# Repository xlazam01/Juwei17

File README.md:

<div align="center">
  <h1>Juwei17 Mount Upgrade</h1>
  
</div>

## 🚀 Project Overview

This repository contains subprojects to upgrade the Juwei17 mount with enhanced hardware, software, and mechanics. The goal is to provide a modern, feature-rich, and user-friendly experience for astronomy enthusiasts.

---

## 🧑‍🔧 Skills Needed

 - Project is very DIY oriented
 - PCB is very dense and it is recommended to manufacture it via some service (JLCPCB or similar)
 - Some soldering (hall sensors, BME280, switch, connector crimping)

---

## ✨ Upgrade Features

- **Larger on/off switch**
- **Homing**
- **GPS**
- **Weather sensors**
- **Fast slewing possible**
- **Support for TMC SPI or UART modules**  
  (TMC2209, TMC2130, TMC5160, etc.)
- **USB-C connector**
- **Programming button** (no ST-Link needed)
- **Loader application** (semi-automatic programming for OnStep and SWS)

---

## 🧩 Hardware Features

- Minimized PCB size
- Support for Home and Limit switches
- OnWire interface
- GPS interface
- STM32F446 as main processor
- Power switch not needed:
  - Mount will start without switch connected
  - No high current goes through switch itself
  - When switch is closed, mount is off

---

## 💾 Software Features

- Based on OnStepX (preconfigured, just upload)
- Added STM32 RTC support
- Modified Weather:
  - Due to excessive BME self-heating
  - Temperature from DS1820
  - Humidity and pressure from BME280
- TLS fallback (STM32 → GPS)
- PlatformIO is used for OnStepX - My preferred IDE
- Arduino for SWS - due to specific version of ESP toolchain needed

---

## 🏗️ Mechanics

- CAD files
- STL files for 3D printing new covers

---

## 📦 Required Components

- New hardware - data on this github repo
- 2x TMC Drivers - you can reuse TMC2209 from your original main board
  - TMC2209 UART - [link](https://www.aliexpress.com/item/33028050145.html)
  - TMC2130 SPI - [link](https://www.aliexpress.com/item/32970150483.html)
  - TMC5160 SPI - [link](https://www.aliexpress.com/item/1005006043696147.html)
- Beitian BK-280 GPS module -  [link](https://www.aliexpress.com/item/1005009032383874.html)
- BME280 module - [link](https://www.aliexpress.com/item/1005007070789246.html)
- DS1820 - [link](https://www.aliexpress.com/item/1005009032259334.html)
- 2× 3144 hall sensors for homing functionality [link](https://www.aliexpress.com/item/1005008305500149.html)
- 16mm antivandal switch - 16mm, 12-24V, latching - [link](https://www.aliexpress.com/item/1005007144363231.html)
- Wires, connectors, hot glue, etc.
- Crimping pliers (Iwiss IWS-2820M)
- Magnetic rings:
  - Magnets 20×5×2mm [link](https://www.aliexpress.com/item/1005009668801201.html)
    ⚠️ *Warning: Large deviation in sizes experienced!*
- Screws M2×6 Voron style self-tapping screws - [link](https://www.aliexpress.com/item/1005003604942716.html)
- 4x M3x16, 4x  M3x10 countersunk
- optional 3144 hall sensor module for test [link](https://www.aliexpress.com/item/1005009110720818.html)
  - 5V power
  - It can help you to check polarity and sensitivity for you DIY magnet rings

---

## 🛠️ Building Tips

- Use hot glue to fix hall sensors and wires
- Mind the hall sensor "polarity" and magnets orientation in rings - good to check with dry run before mounting everything together

---

## 📁 Folder Description

- **CAD**: SolidEdge models (`*.par` files)
- **HW**: KiCad files (design and schematic PDF)
- **Images**: Build images
- **OnstepEspLoader**: Python app to support you through flashing process
- **OnStepX**: OnStep code (PlatformIO and VSCode)
- **SmartWebServer**: ESP8266 code (built in Arduino due to specific Espressif version)
- **STLs**: Files for 3D printing

---

## 📝 ToDo

- PEC

---

## 🖼️ Photo Gallery
<div align="center">
    
</div>

<div align="center">

</div>
<div align="center">

</div>
<div align="center">

</div>
<div align="center">

</div>
<div align="center">

</div>
<div align="center">

</div>

---

## 🛠️ Assembly Instructions

1. **Print the required parts.**
2. **Prepare magnets for the magnet rings:**
    - Ensure all magnets are oriented in the same direction.
    - Take care to prevent magnets from snapping together unexpectedly.
    - Test magnet polarity using a 3144 module or a bare sensor.
3. **Insert magnets into the rings.**
    - Fill roughly 90-180degrees
4. **Secure magnets with a thin layer of epoxy.**
    - 5min epoxy is ideal
5. **Assemble the front cover using small screws.**
    - Put together PCB_holder and front_panel
6. **Install hall sensors and wiring into the new cover.**
    - Insert hall sensor with right orientation (double check)
    - Fix them in place with hotglue
7. **Mount the new 16mm switch and do wiring.**
    - We use NO contact for mount ON, NC contact for mount OFF
    - Switch backlight is connected to mainboard
8. **Prepare and install wiring for the GPS and BME280 modules.**
    - Solder longer wires and cut them later to perfect length for BME280
    - For GPS just cut the wire to perfect length
    - Install modules in cavities
    - Fix GPS with GPS_holder and small screws
9. **Install the DS1820 sensor in the second cover.**
    - Pressfit the sensor in place
    - Cut wires to size
10. **Secure all wires with hot glue.**
    - Aim is to not have wires getting pinched during cover installation
11. **Trim wires to length and crimp connectors.**
12. **Plug in jumper for UART/SPI TMC**
13. **Insert TMC modules**
14. **PCB installation**
    - Reuse brass standoff - insert them into holes in front cover
    - Attach the PCB to these standoffs    
15. **Connect all components together.**
    - Install back cover
    - Plug in all connectors
    - Install front cover
    - Screw in four screws for the PCB from the bottom of the mount
16. **Assembly complete!**

---

<div align="center">
    
</div>

## 💻 Firmware Upload

1. **Power off the device.**
2. **Press and hold the button** next to the power connector.
3. **Power on the device.**
4. **Observe the LEDs:**
    - OnStep status LED will be off.
    - WiFi LED will blink if firmware is present; if the ESP is empty, both LEDs will be off.
5. **Start the OnstepEspLoader Python app.**
6. **Select the correct TMC module type.**
7. **Choose homing**
8. **Click "Check STM32":**
    - The bootloader should respond.
    - If it fails, click again.
9. **Click "Upload STM32":**
    - Firmware upload will start.
10. **Wait for the OnStep status LED:**
    - It should turn on after some time.
    - The first boot may take longer as EEPROM is being formatted.
11. **Click "Check OnStep":**
    - It should respond with name and version.
12. **Switch to SWS mode:**
    - OnStep enters transparent mode and is ready to upload ESP firmware.
13. **Click "Upload ESP":**
    - Firmware for the webserver will be uploaded to the ESP.
14. **Finish:**
    - A soft reset will occur after some time, or you can power cycle the device manually.

---

## ⚙️ Default Firmware Configuration

Default firmware configuration expects:
- BME280, DS1820 - if initialization fails, there will be no weather information on webserver
- TMC2209, TMC5160 or TMC2130 - according to selected firmware during programming
- Correct polarity of HAL sensors for homing - if not fulfilled, homing will not work correctly
- Motor current is set to 1.0A for RUN and 1.3A for GOTO
- Homing sense is HIGH

---

## 🏗️ Build Your Own OnStepX

- If you use OnStepX from Howard Dutton - there will be no support for STM32 RTC (time and date will not be stored) and weather service will provide false temperatures from BME280 (self-heating)
 - This could be potentially merged into main branch (I know that STM32 RTC was not planned - there are no official boards ready for this, weather fix is open)
- For my Juwei17 board use the OnStepX from this repository
- Change configuration as needed
- For upload use Serial Bootloader - depending on your IDE (Arduino, PlatformIO) how to do it 
- There are three pads on the bottom of the PCB to connect to ST-Link - you need to solder wires or a connector with 2mm pitch
- If you want to use OnstepEspLoader just browse for your STM32 firmware binary
- Binary file pattern:

| Firmware Name         | TMC Module | Homing      |
|-----------------------|------------|-------------|
| firmware_5160_wH      | TMC5160    | With Homing |
| firmware_5160_woH     | TMC5160    | Without Homing |
| firmware_2130_wH      | TMC2130    | With Homing |
| firmware_2130_woH     | TMC2130    | Without Homing |
| firmware_2209_wH      | TMC2209    | With Homing |
| firmware_2209_woH     | TMC2209    | Without Homing |

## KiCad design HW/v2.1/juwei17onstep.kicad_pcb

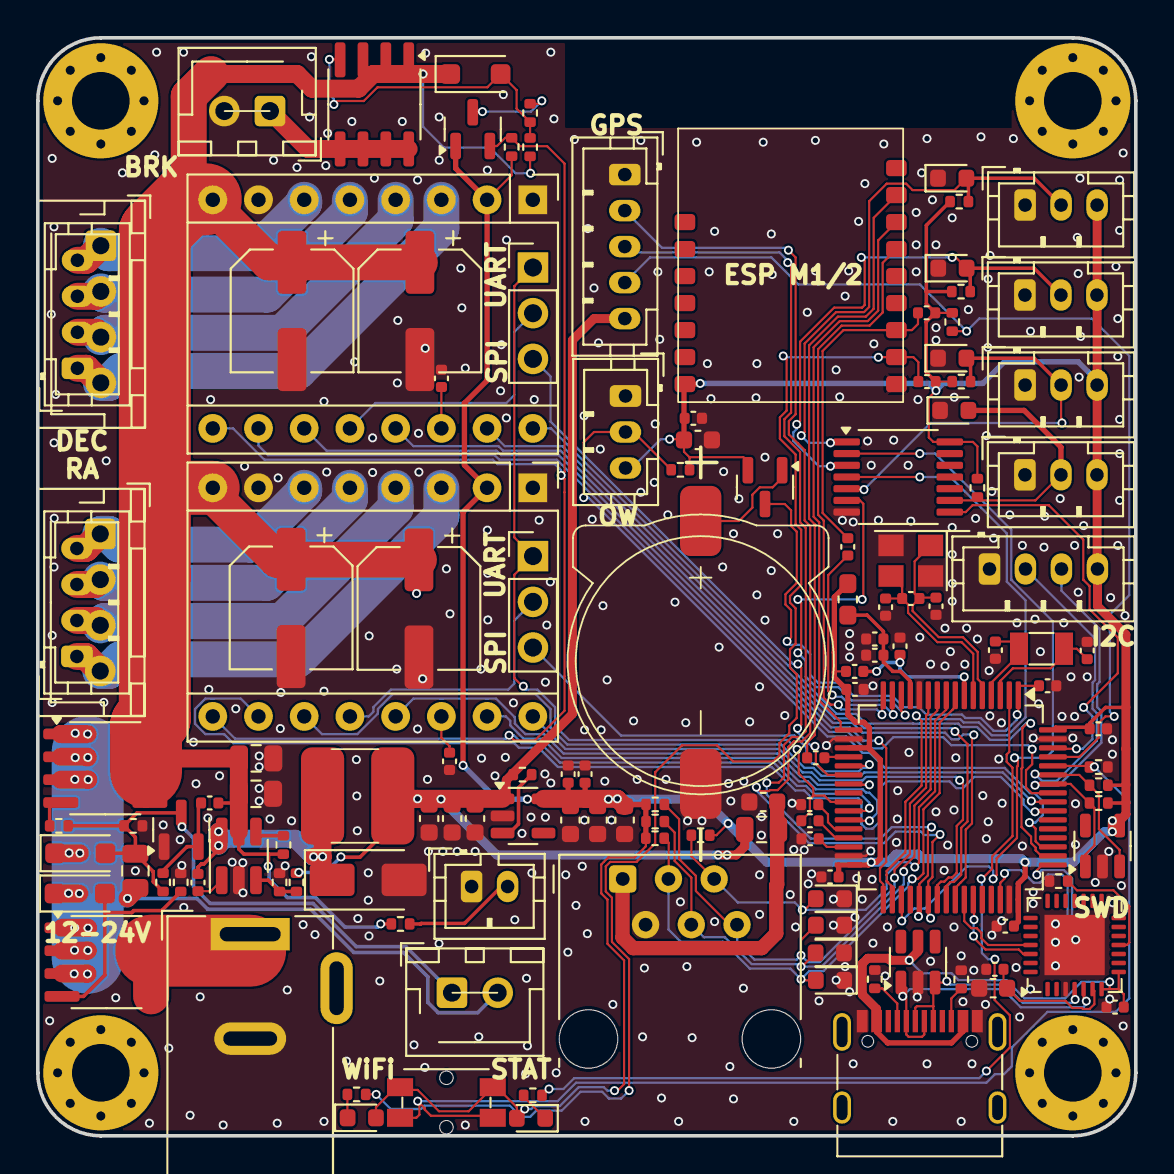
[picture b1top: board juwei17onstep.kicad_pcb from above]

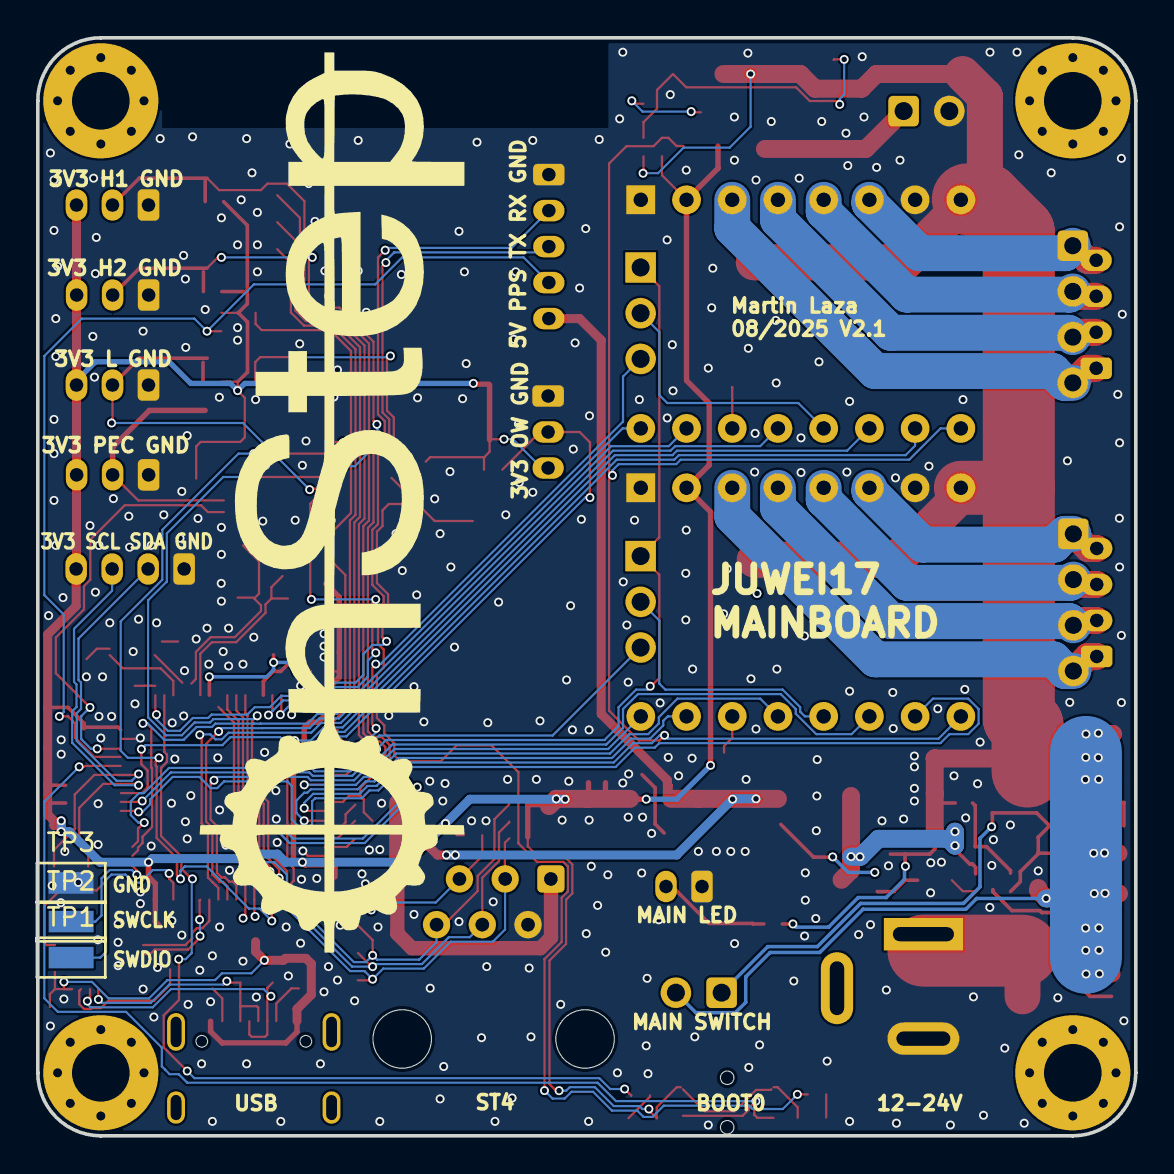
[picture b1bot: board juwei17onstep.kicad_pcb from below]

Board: 2 copper layers, 61.0 x 61.0 mm, 139 parts (3 on the bottom side), 97 nets.

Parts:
A1, A2: Pololu_Breakout_A4988; StepStick
BT1: Battery_Cell; CR1220_holder
C1, C4: 20pF; C_0402_1005Metric
C2, C19: 10u/25V; C_0805_2012Metric
C3, C11, C14, C15, C16, C18, C22, C26, C49: 10uF/10V; C_0603_1608Metric
C5, C13: 1uF/10V; C_0402_1005Metric
C6, C7: 2u2/6.3; C_0402_1005Metric
C8, C9: 12pF; C_0402_1005Metric
C10, C12, C20, C21, C40, C46, C47: 100n; C_0402_1005Metric
C17, C23, C41: 100n/50V; C_0402_1005Metric
C24: 1u/25V; C_0805_2012Metric
C25: 1uF; C_0402_1005Metric
C27: 100nF; C_0402_1005Metric
C28, C42, C43, C44: 100uF/35V; CP_Elec_6.3x7.7
D1, D15: LED; LED_0603_1608Metric
D2: SS34; D_SMA
D3, D4, D5, D6, D8, D9, D10, D14: 0603ESDA-05N; D_0603_1608Metric
D7, D16: BZT52B12; D_SOD-123F
D11: BZT52Bxx; D_SOD-123F
D13: BAT54C; SOT-23
D17: BAV99; SOT-23
F1: SMD0805P050TF; Fuse_0805_2012Metric
H1, H2, H3, H4: MountingHole; MountingHole_3.2mm_M3_Pad_Via
J1: USB_C_Receptacle_USB2.0; USB_C_Receptacle_G-Switch_GT-USB-7010ASV
J2: RJ12; RJ12_Amphenol_54601-x06_Horizontal
J3: 5.5/2.1 Barell DC3; BarrelJack_Wuerth_6941xx301002
J4: RA_HOME; JST_PH_B3B-PH-K_1x03_P2.00mm_Vertical
J5: DEC_HOME; JST_PH_B3B-PH-K_1x03_P2.00mm_Vertical
J6: LIMIT; JST_PH_B3B-PH-K_1x03_P2.00mm_Vertical
J7: GPS; JST_PH_B5B-PH-K_1x05_P2.00mm_Vertical
J8: Conn_01x02; JST_1x02_P2.54
J10: MAIN SWITCH; JST_1x02_P2.54
J11, J12: RA_2mm; JST_PH_B4B-PH-K_1x04_P2.00mm_Vertical
J13, J14: RA_2.54mm; JST_1x04_P2.54
J15: I2C; JST_PH_B4B-PH-K_1x04_P2.00mm_Vertical
J16: LED CONNECTOR; JST_PH_B2B-PH-K_1x02_P2.00mm_Vertical
J17: PEC; JST_PH_B3B-PH-K_1x03_P2.00mm_Vertical
J18: ONEWIRE; JST_PH_B3B-PH-K_1x03_P2.00mm_Vertical
JP1, JP2: SolderJumper_3_Open; PinHeader_1x03_P2.54mm_Vertical
L2: FNR5040S100MT; L_5.5x5.1mm
L3: BLM18HE601SH1D; L_0603_1608Metric_Pad1.05x0.95mm_HandSolder
Q1, Q2, Q4: AO4411; SOIC-8_3.9x4.9mm_P1.27mm
Q3: DTC114E; SOT-23
R1: 1MEG; C_0402_1005Metric
R2, R3, R4, R5, R36, R37: 10k; C_0402_1005Metric
R6, R21, R25, R26, R27, R33, R34, R38: 10k; R_0402_1005Metric
R7, R8, R39: 5k1; R_0402_1005Metric
R9, R18, R44, R45: 1k; R_0402_1005Metric
R10, R11, R31, R43: 100k; R_0402_1005Metric
R14: 36k; R_0402_1005Metric
R15: 6k8; R_0402_1005Metric
R16, R17, R19, R32: 4k7; R_0402_1005Metric
R20, R22, R23, R24: 2k4; R_0402_1005Metric
R28, R29, R42: 1k; C_0402_1005Metric
R35: 510R; R_0402_1005Metric
RST2: EVQPUM; Panasonic_EVQPUM_EVQPUD
TP1, TP2, TP3: TestPoint; TestPoint_Keystone_5015_Micro-Minature
U1: ESP_M2
U2: CP2102N-Axx-xQFN28; QFN-28-1EP_5x5mm_P0.5mm_EP3.35x3.35mm
U5: USBLC6-2SC6; SOT-23-6
U6: 74HC14; TSSOP-14_4.4x5mm_P0.65mm
U7: ME6211; SOT-23-5
U8: ME3116; SOT-23-6_Handsoldering
U9: 24AA64T-I/OT; SOT-23-5
U12: STM32F446RETx; LQFP-64_10x10mm_P0.5mm
Y1: TAXM8M4RDBCCT2T / 8MHz 3225; Crystal_SMD_3225-4Pin_3.2x2.5mm
Y2: Crystal; Crystal_SMD_3215-2Pin_3.2x1.5mm

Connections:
/3V3: A1.2 (VDD), A2.2 (VDD), C10.1, C12.1, C13.2, C14.2, C15.2, C16.2, C20.1, C21.1, C22.2, C40.1, C41.2, D1.2 (A), D13.2, D15.2 (A), J4.3, J5.3, J6.3, J15.4, J17.3, J18.3, L3.1, Q3.1 (B), R2.2, R3.2, R5.2, R16.2, R17.2, R19.2, R20.2, R22.2, R23.2, R24.2, R25.2, R26.2, R27.2, R33.2, R34.2, R38.2, RST2.2, U1.7 (VCC), U6.14 (VCC), U7.5 (OUT), U9.4 (V_{CC}), U12.19 (VDD), U12.32 (VDD), U12.48 (VDD), U12.64 (VDD)
/DEC/DIR: A2.16 (DIR), U12.50 (PA15)
/DEC/ENN: A1.9 (~ENABLE), A2.9 (~ENABLE), Q3.2 (E), R38.1, U12.26 (PB0)
/DEC/M0: A2.10 (CFG1), U12.57 (PB5)
/DEC/M1: A2.11 (CFG2), U12.33 (PB12)
/DEC/M2: JP2.3 (B), U12.22 (PA6)
/DEC/M3: A2.13 (CFG0), U12.41 (PA8)
/DEC/STEP: A2.15 (STEP), U12.40 (PC9)
/DEC/TMC_UART: JP1.1 (A), JP2.1 (A), R42.1, U12.25 (PC5)
/DEC/VM: A1.8 (VMOT), A2.8 (VMOT), C2.1, C19.1, C23.2, C28.1, C42.1, C43.1, C44.1, D11.1 (K), Q2.1 (S), Q2.2 (S), Q2.3 (S), Q4.5 (D), Q4.6 (D), Q4.7 (D), Q4.8 (D), R10.2, R31.2, R35.2, U8.5 (VIN)
/ESP_BOOT: R29.2, U12.15 (PA1)
/ESP_RST: R28.1, U12.20 (PA4)
/ESP_RXD: U1.13 (RXD0), U12.16 (PA2)
/ESP_TXD: U1.14 (TXD0), U12.17 (PA3)
/GPS_RXD: J7.2, U12.38 (PC7)
/GPS_TXD: J7.3, U12.37 (PC6)
/ME3116/VOUT: C3.2, C18.2, C49.2, F1.2, J7.5, L2.2, R11.2, R14.2, U7.1 (IN)
/OnStep_MaxSTM/AXIS1_DIR: A1.16 (DIR), U12.39 (PC8)
/OnStep_MaxSTM/AXIS1_HOME_SW: U6.2, U12.35 (PB14)
/OnStep_MaxSTM/AXIS1_M0: A1.10 (CFG1), U12.55 (PB3)
/OnStep_MaxSTM/AXIS1_M1: A1.11 (CFG2), U12.56 (PB4)
/OnStep_MaxSTM/AXIS1_M2: JP1.3 (B), U12.21 (PA5)
/OnStep_MaxSTM/AXIS1_M3: A1.13 (CFG0), U12.23 (PA7)
/OnStep_MaxSTM/AXIS1_STEP: A1.15 (STEP), U12.27 (PB1)
/OnStep_MaxSTM/AXIS2_HOME_SW: U6.4, U12.34 (PB13)
/OnStep_MaxSTM/BOOT0: R6.2, RST2.1, U12.60 (BOOT0)
/OnStep_MaxSTM/LIMIT_SW: U6.6, U12.14 (PA0)
/OnStep_MaxSTM/M: J1.A7 (D-), J1.B7 (D-), U2.5 (D-), U5.1 (I/O1)
/OnStep_MaxSTM/NRST: C5.1, R2.1, U12.7 (NRST)
/OnStep_MaxSTM/ONEWIRE: J18.2, R19.1, U12.51 (PC10)
/OnStep_MaxSTM/OSC32_IN: C8.1, U12.3 (PC14), Y2.1
/OnStep_MaxSTM/OSC32_OUT: C9.1, U12.4 (PC15), Y2.2
/OnStep_MaxSTM/OSCIN: C1.1, R1.1, U12.5 (PH0), Y1.1
/OnStep_MaxSTM/OSCOUT: C4.1, R1.2, U12.6 (PH1), Y1.3
/OnStep_MaxSTM/P: J1.A6 (D+), J1.B6 (D+), U2.4 (D+), U5.3 (I/O2)
/OnStep_MaxSTM/PEC_SENSE: U6.8, U12.62 (PB9)
/OnStep_MaxSTM/RX1: U2.26 (TXD), U12.43 (PA10)
/OnStep_MaxSTM/SCL: J15.3, R17.1, U9.1 (SCL), U12.58 (PB6)
/OnStep_MaxSTM/SDA: J15.2, R16.1, U9.3 (SDA), U12.59 (PB7)
/OnStep_MaxSTM/ST4_DEC_N: D5.2 (A2), J2.5, R23.1, U12.9 (PC1)
/OnStep_MaxSTM/ST4_DEC_S: D4.2 (A2), J2.4, R22.1, U12.10 (PC2)
/OnStep_MaxSTM/ST4_RA_E: D6.2 (A2), J2.6, R24.1, U12.11 (PC3)
/OnStep_MaxSTM/ST4_RA_W: D3.2 (A2), J2.3, R20.1, U12.8 (PC0)
/OnStep_MaxSTM/STATUS_LED: R9.1, U12.2 (PC13)
/OnStep_MaxSTM/SWCLK: TP2.1, U12.49 (PA14)
/OnStep_MaxSTM/SWDIO: TP1.1, U12.46 (PA13)
/OnStep_MaxSTM/TX1: U2.25 (RXD), U12.42 (PA9)
/OnStep_MaxSTM/VBATT: C47.1, D13.3, U12.1 (VBAT)
/OnStep_MaxSTM/VBUS: C25.2, J1.A4 (VBUS), J1.A9 (VBUS), J1.B4 (VBUS), J1.B9 (VBUS), U2.7 (VREGIN), U2.8 (VBUS), U5.5 (VBUS)
/OnStep_MaxSTM/VREF: C7.1, C46.1, L3.2, U12.13 (VDDA)
/PPS: J7.4, R34.1, U12.61 (PB8)
/VBAT: BT1.1 (+), D13.1
GND: A1.1 (GND), A1.7 (GND), A2.1 (GND), A2.7 (GND), BT1.2 (-), C1.2, C2.2, C3.1, C4.2, C5.2, C6.2, C7.2, C8.2, C9.2, C10.2, C11.2, C12.2, C13.1, C14.1, C15.1, C16.1, C18.1, C19.2, C20.2, C21.2, C22.1, C25.1, C26.2, C27.2, C28.2, C40.2, C41.1, C42.2, C43.2, C44.2, C46.2, C47.2, C49.1, D2.2 (A), D3.1 (A1), D4.1 (A1), D5.1 (A1), D6.1 (A1), D8.1 (A1), D9.1 (A1), D10.1 (A1), D14.1 (A1), D17.1 (K), J1.A1 (GND), J1.A12 (GND), J1.B1 (GND), J1.B12 (GND), J2.2, J3.2, J4.1, J5.1, J6.1, J7.1, J8.2, J15.1, J16.1, J17.1, J18.1, R4.1, R6.1, R7.2, R8.2, R15.1, R21.1, R36.1, R37.1, R39.1, R43.2, TP3.1, U1.8 (GND), U2.3 (GND), U2.29 (GND), U5.2 (GND), U6.7 (GND), U7.2 (GND), U8.2 (GND), U9.2 (V_{SS}), U12.12 (VSSA), U12.18 (VSS), U12.31 (VSS), U12.47 (VSS), U12.63 (VSS), Y1.2, Y1.4
unnamed: A1.4 (1A), J11.2, J13.3
unnamed: A1.3 (1B), J11.1, J13.4
unnamed: A1.5 (2A), J11.3, J13.2
unnamed: A1.6 (2B), J11.4, J13.1
unnamed: A1.12 (CFG3), JP1.2 (C)
unnamed: A1.14 (CLK), R36.2
unnamed: A2.4 (1A), J12.2, J14.3
unnamed: A2.3 (1B), J12.1, J14.4
unnamed: A2.5 (2A), J12.3, J14.2
unnamed: A2.6 (2B), J12.4, J14.1
unnamed: A2.12 (CFG3), JP2.2 (C)
unnamed: A2.14 (CLK), R37.2
unnamed: C11.1, F1.1, J2.1
unnamed: D1.1 (K), R9.2
unnamed: C17.2, D2.1 (K), L2.1, U8.6 (SW)
unnamed: D7.2 (A), Q1.4 (G), R21.2
unnamed: D8.2 (A2), J4.2, R25.1, U6.1
unnamed: D9.2 (A2), J5.2, R26.1, U6.3
unnamed: D10.2 (A2), J6.2, R27.1, U6.5
unnamed: D11.2 (A), Q2.4 (G), R31.1, R32.2
unnamed: D14.2 (A2), J17.2, R33.1, U6.9
unnamed: D15.1 (K), R18.2
unnamed: C24.2, D16.2 (A), D17.3 (K), J10.1, R43.1, R44.1, R45.2
unnamed: C24.1, D7.1 (K), D16.1 (K), J10.2, Q1.1 (S), Q1.2 (S), Q1.3 (S), Q4.1 (S), Q4.2 (S), Q4.3 (S)
unnamed: C23.1, D17.2 (A), R45.1
unnamed: J1.A5 (CC1), R7.1
unnamed: J1.B5 (CC2), R8.1
unnamed: J3.1, Q1.5 (D), Q1.6 (D), Q1.7 (D), Q1.8 (D)
unnamed: J8.1, Q2.5 (D), Q2.6 (D), Q2.7 (D), Q2.8 (D)
unnamed: J16.2, R35.1
unnamed: Q3.3 (C), R32.1
unnamed: Q4.4 (G), R44.2
unnamed: R3.1, R29.1, U1.10 (IO0)
unnamed: R5.1, R18.1, U1.9 (IO2)
unnamed: R28.2, U1.15 (RST)
unnamed: C26.1, C27.1, U2.6 (VDD)
unnamed: R39.2, U2.11 (~SUSPEND)
unnamed: R11.1, U7.3 (EN)
unnamed: C17.1, U8.1 (BS)
unnamed: R10.1, U8.4 (EN)
unnamed: R14.1, R15.2, U8.3 (FB)
unnamed: R4.2, U12.28 (PB2)
unnamed: R42.2, U12.29 (PB10)
unnamed: C6.1, U12.30 (VCAP_1)

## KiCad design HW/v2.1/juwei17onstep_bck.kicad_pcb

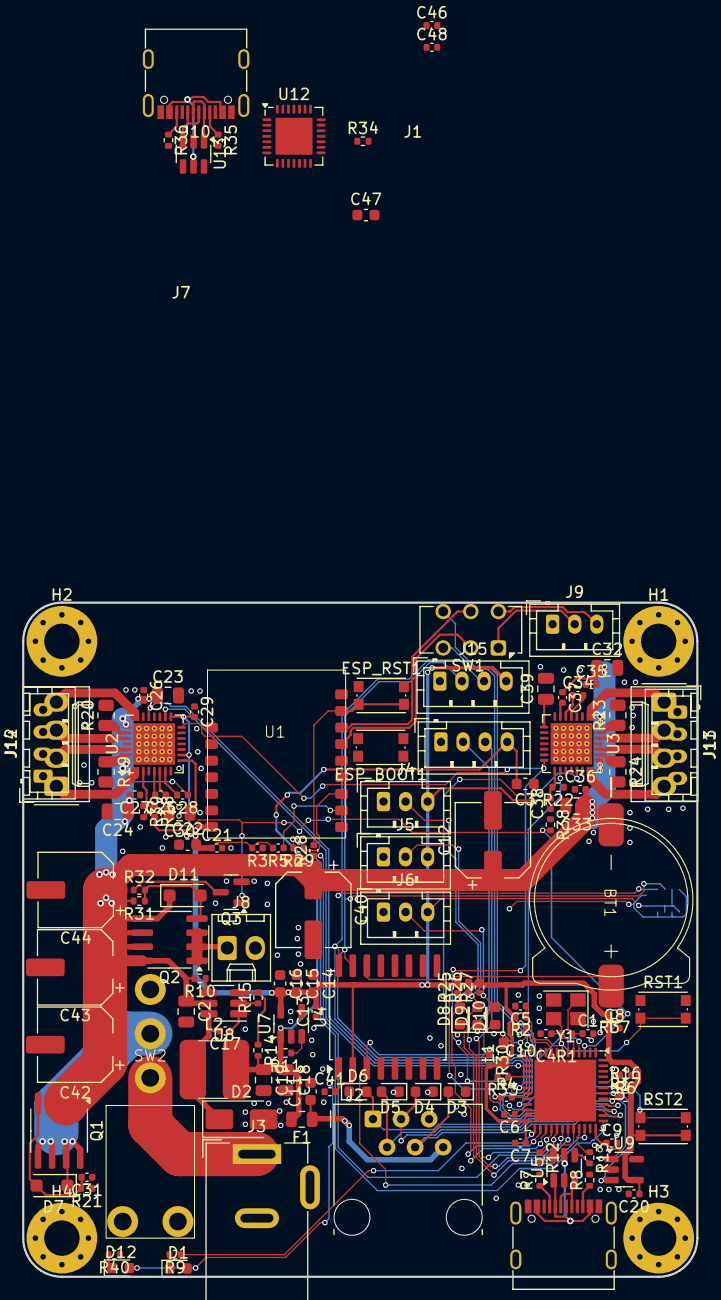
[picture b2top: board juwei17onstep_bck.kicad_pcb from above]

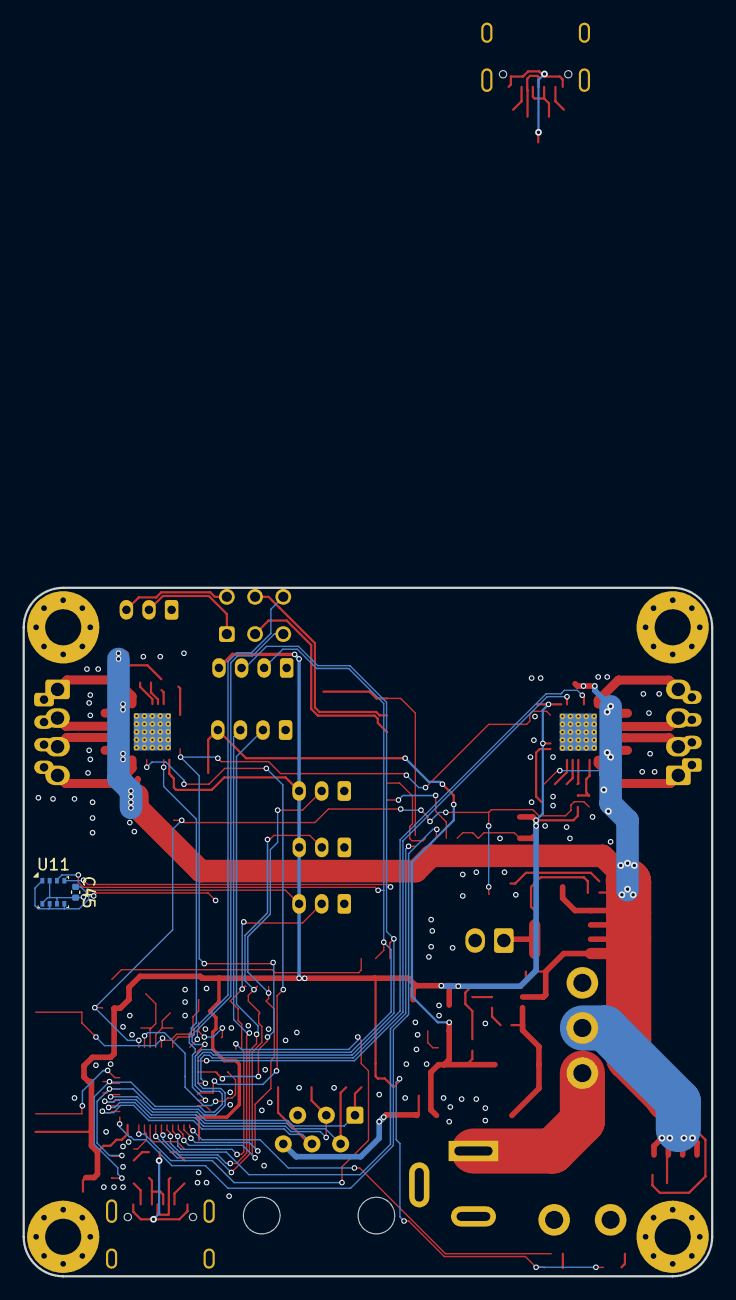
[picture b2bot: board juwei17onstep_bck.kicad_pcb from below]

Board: 2 copper layers, 61.0 x 61.0 mm, 145 parts (2 on the bottom side), 96 nets.

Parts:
BT1: Battery_Cell; CR1220_holder
C1, C4: 20pF; C_0402_1005Metric
C2, C18, C19: 10u/25V; C_0805_2012Metric
C3, C11, C14, C15, C16, C22, C47: 10uF/10V; C_0603_1608Metric
C5, C13: 1uF/10V; C_0402_1005Metric
C6: 2u2/6.3; C_0402_1005Metric
C7, C8, C9, C10, C20, C21: 100n; C_0402_1005Metric
C12, C40, C42, C43, C44: 100uF/35V; CP_Elec_6.3x7.7
C17: 100n/50V/0603; C_0402_1005Metric
C23, C24, C30, C32, C33, C39: 4.7u/25V; C_0805_2012Metric
C25, C31, C34: 22n/50V; C_0402_1005Metric
C26, C27, C28, C29, C35, C36, C37, C38, C41: 100n/50V; C_0402_1005Metric
C45, C48: 100nF; C_0402_1005Metric
C46: 1uF; C_0402_1005Metric
D1, D12: LED; LED_0603_1608Metric
D2: SS34; D_SMA
D3, D4, D5, D6, D8, D9, D10: 0603ESDA-05N; D_0603_1608Metric
D7: BZT52B12; D_SOD-123F
D11: BZT52Bxx; D_SOD-123F
ESP_BOOT1: EVQPUM; SW_Push_1P1T_NO_CK_KMR2
ESP_RST1: EVQPUM; SW_Push_1P1T_NO_CK_KMR2
F1: SMD0805P050TF; Fuse_0805_2012Metric
H1, H2, H3, H4: MountingHole; MountingHole_3.2mm_M3_Pad_Via
J1, J10: USB_C_Receptacle_USB2.0; USB_C_Receptacle_G-Switch_GT-USB-7010ASV
J2: RJ12; RJ12_Amphenol_54601-x06_Horizontal
J3: 5.5/2.1 Barell DC3; BarrelJack_Wuerth_6941xx301002
J4: RA_HOME; JST_PH_B3B-PH-K_1x03_P2.00mm_Vertical
J5: DEC_HOME; JST_PH_B3B-PH-K_1x03_P2.00mm_Vertical
J6: LIMIT; JST_PH_B3B-PH-K_1x03_P2.00mm_Vertical
J7: GPS; JST_PH_B4B-PH-K_1x04_P2.00mm_Vertical
J8: Conn_01x02; Molex_KK-254_AE-6410-02A_1x02_P2.54mm_Vertical
J9: ESP_UART; JST_PH_B3B-PH-K_1x03_P2.00mm_Vertical
J11, J12: RA_2mm; JST_PH_B4B-PH-K_1x04_P2.00mm_Vertical
J13, J14: RA_2.54mm; Molex_KK-254_AE-6410-04A_1x04_P2.54mm_Vertical
J15: I2C; JST_PH_B4B-PH-K_1x04_P2.00mm_Vertical
L1: BLM18HE601SH1D; L_0603_1608Metric_Pad1.05x0.95mm_HandSolder
L2: FNR5040S100MT; L_5.5x5.1mm
Q1, Q2: AO4411; SOIC-8_3.9x4.9mm_P1.27mm
Q3: DTC114E; SOT-23
R1: 1MEG; C_0402_1005Metric
R2, R3, R4, R5: 10k; C_0402_1005Metric
R6, R21, R25, R26, R27, R34: 10k; R_0402_1005Metric
R7, R8, R35, R36: 5k1; R_0402_1005Metric
R9, R38, R39, R40: 1k; R_0402_1005Metric
R10, R11, R18, R22, R31, R37: 100k; R_0402_1005Metric
R12, R13: 22R; R_0402_1005Metric
R14: 36k; R_0402_1005Metric
R15: 6k8; R_0402_1005Metric
R16, R17, R30, R32: 4k7; R_0402_1005Metric
R19, R20, R23, R24: 0.11R/0805; R_0805_2012Metric
R28, R29, R33: 1k; C_0402_1005Metric
RST1, RST2: EVQPUM; SW_Push_1P1T_NO_CK_KMR2
SW1: SW_Slide_DPDT; SW_CK_JS202011CQN_DPDT_Straight
SW2: SW_SPST; MTS-102-C4
U1: ESP_M2
U2, U3: QFN-28-1EP_5x5mm_P0.5mm_EP3.75x3.75mm_ThermalVias
U4: DS3231M; SOIC-16W_7.5x10.3mm_P1.27mm
U5, U13: USBLC6-2SC6; SOT-23-6
U6: STM32F411CCUx; QFN-48-1EP_7x7mm_P0.5mm_EP5.6x5.6mm
U7: ME6211; SOT-23-5
U8: ME3116; SOT-23-6_Handsoldering
U9: 24AA64T-I/OT; SOT-23-5
U11: BME280; Bosch_LGA-8_2.5x2.5mm_P0.65mm_ClockwisePinNumbering
U12: CP2102N-Axx-xQFN28; QFN-28-1EP_5x5mm_P0.5mm_EP3.35x3.35mm
Y1: TAXM8M4RDBCCT2T / 8MHz 3225; Crystal_SMD_3225-4Pin_3.2x2.5mm

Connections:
/3V3: C7.1, C8.1, C9.1, C13.2, C14.2, C15.2, C16.2, C20.1, C21.1, C22.2, C29.2, C38.2, C41.2, C45.2, D1.2 (A), D12.2 (A), J4.3, J5.3, J6.3, J15.4, L1.1, R2.2, R3.2, R5.2, R16.2, R17.2, R18.2, R22.2, R25.2, R26.2, R27.2, R30.2, R37.2, RST2.2, U1.7 (VCC), U2.9 (MS1_AD0), U2.15 (VCC_IO), U3.15 (VCC_IO), U4.2 (VCC), U6.24 (VDD), U6.36 (VDD), U6.48 (VDD), U7.5 (OUT), U9.4 (V_{CC}), U11.2 (CSB), U11.6 (VDDIO), U11.8 (VDD)
/DEC/DIR: U2.19 (DIR), U6.18 (PB0)
/DEC/ENN: Q3.1 (B), R37.1, R38.2, R39.2, U6.3 (PC14)
/DEC/OUTA1: J12.3, J14.3, U2.24 (OUTA1)
/DEC/OUTA2: J12.4, J14.4, U2.21 (OUTA2)
/DEC/OUTB1: J12.2, J14.2, U2.26 (OUTB1)
/DEC/OUTB2: J12.1, J14.1, U2.1 (OUTB2)
/DEC/STEP: U2.16 (STEP), U6.14 (PA4)
/DEC/TMC_UART: R33.1, U2.14 (PDN_UART), U3.14 (PDN_UART), U6.16 (PA6)
/DEC/VM: C2.1, C12.1, C23.1, C24.1, C26.2, C27.2, C28.1, C32.1, C33.1, C35.2, C36.2, C37.1, C40.1, C42.1, C43.1, C44.1, D11.1 (K), Q1.1 (S), Q1.2 (S), Q1.3 (S), Q2.5 (D), Q2.6 (D), Q2.7 (D), Q2.8 (D), R10.2, R31.2, U2.22 (VS), U2.28 (VS), U3.22 (VS), U3.28 (VS), U8.5 (VIN)
/ESP_BOOT: R29.2, U6.37 (PA14)
/ESP_RST: R28.1, U6.29 (PA8)
/ESP_RXD: SW1.4 (A), U6.13 (PA3)
/ESP_TXD: SW1.3 (C), U6.12 (PA2)
/GND: BT1.2 (-), C1.2, C2.2, C3.1, C4.2, C5.2, C6.2, C7.2, C8.2, C9.2, C10.2, C11.2, C12.2, C13.1, C14.1, C15.1, C16.1, C18.2, C19.2, C20.2, C21.2, C22.1, C23.2, C24.2, C26.1, C27.1, C29.1, C30.2, C31.1, C32.2, C33.2, C35.1, C36.1, C38.1, C39.2, C40.2, C41.1, C42.2, C43.2, C44.2, C45.1, C46.1, C47.2, C48.2, D2.2 (A), D3.1 (A1), D4.1 (A1), D5.1 (A1), D6.1 (A1), D8.1 (A1), D9.1 (A1), D10.1 (A1), ESP_BOOT1.1, ESP_RST1.1, J1.A1 (GND), J1.A12 (GND), J1.B1 (GND), J1.B12 (GND), J2.5, J3.2, J4.1, J5.1, J6.1, J7.1, J8.2, J9.1, J10.A1 (GND), J10.A12 (GND), J10.B1 (GND), J10.B12 (GND), J15.1, Q3.2 (E), R4.1, R6.1, R7.2, R8.2, R15.1, R19.2, R20.2, R21.1, R23.2, R24.2, R34.1, R35.2, R36.2, R40.1, RST1.1, U1.8 (GND), U2.3 (GND), U2.10 (MS2_AD1), U2.13 (CLK), U2.18 (GND), U2.29 (GND), U3.3 (GND), U3.9 (MS1_AD0), U3.10 (MS2_AD1), U3.13 (CLK), U3.18 (GND), U3.29 (GND), U4.5 (GND), U4.6 (GND), U4.7 (GND), U4.8 (GND), U4.9 (GND), U4.10 (GND), U4.11 (GND), U4.12 (GND), U4.13 (GND), U5.2 (GND), U6.8 (VSSA), U6.23 (VSS), U6.35 (VSS), U6.47 (VSS), U6.49 (VSS), U7.2 (GND), U8.2 (GND), U9.2 (V_{SS}), U11.1 (GND), U11.5 (SDO), U11.7 (GND), U12.3 (GND), U12.29 (GND), U13.2 (GND), Y1.2, Y1.4
/GPS_RXD: J7.2, U6.31 (PA10)
/GPS_TXD: J7.3, U6.30 (PA9)
/ME3116/VOUT: C3.2, C18.1, C19.1, F1.2, J7.4, L2.2, R11.2, R14.2, U7.1 (IN)
/OnStep_MaxSTM/AXIS1_DIR: R4.2, U3.19 (DIR), U6.20 (PB2)
/OnStep_MaxSTM/AXIS1_HOME_SW: D8.2 (A2), J4.2, R25.1, U6.26 (PB13)
/OnStep_MaxSTM/AXIS1_STEP: U3.16 (STEP), U6.21 (PB10)
/OnStep_MaxSTM/AXIS2_HOME_SW: D9.2 (A2), J5.2, R26.1, U6.27 (PB14)
/OnStep_MaxSTM/BOOT0: R6.2, RST2.1, U6.44 (BOOT0)
/OnStep_MaxSTM/DM: R12.2, U5.6 (I/O1)
/OnStep_MaxSTM/DP: R13.2, U5.4 (I/O2)
/OnStep_MaxSTM/LIMIT_SW: D10.2 (A2), J6.2, R27.1, U6.28 (PB15)
/OnStep_MaxSTM/NRST: C5.1, R2.1, RST1.2, U6.7 (NRST)
/OnStep_MaxSTM/OSCIN: C1.1, R1.1, U6.5 (PH0), Y1.1
/OnStep_MaxSTM/OSCOUT: C4.1, R1.2, U6.6 (PH1), Y1.3
/OnStep_MaxSTM/PPS_SENSE: R30.1, U4.3 (~INT/SQW), U6.34 (PA13)
/OnStep_MaxSTM/SCL: J15.3, R17.1, U4.16 (SCL), U6.42 (PB6), U9.1 (SCL), U11.4 (SCK)
/OnStep_MaxSTM/SDA: J15.2, R16.1, U4.15 (SDA), U6.43 (PB7), U9.3 (SDA), U11.3 (SDI)
/OnStep_MaxSTM/ST4_DEC_N: D5.2 (A2), J2.2, U6.40 (PB4)
/OnStep_MaxSTM/ST4_DEC_S: D4.2 (A2), J2.3, U6.39 (PB3)
/OnStep_MaxSTM/ST4_RA_E: D6.2 (A2), J2.1, U6.41 (PB5)
/OnStep_MaxSTM/ST4_RA_W: D3.2 (A2), J2.4, U6.38 (PA15)
/OnStep_MaxSTM/STATUS_LED: R9.1, U6.25 (PB12)
/OnStep_MaxSTM/VREF: C10.1, L1.2, U6.9 (VDDA)
/RA/OUTA1: J11.3, J13.3, U3.24 (OUTA1)
/RA/OUTA2: J11.4, J13.4, U3.21 (OUTA2)
/RA/OUTB1: J11.2, J13.2, U3.26 (OUTB1)
/RA/OUTB2: J11.1, J13.1, U3.1 (OUTB2)
/esp_m1/RX1: J9.2, SW1.1 (A), U12.26 (TXD)
/esp_m1/RXD0: SW1.2 (B), U1.13 (RXD0)
/esp_m1/TX1: J9.3, SW1.6 (C), U12.25 (RXD)
/esp_m1/TXD0: SW1.5 (B), U1.14 (TXD0)
/esp_m1/VBUS: C46.2, J10.A4 (VBUS), J10.A9 (VBUS), J10.B4 (VBUS), J10.B9 (VBUS), U12.7 (VREGIN), U12.8 (VBUS), U13.5 (VBUS)
/i2c_per/VBAT: BT1.1 (+), U4.14 (VBAT)
unnamed: C11.1, F1.1, J2.6
unnamed: D1.1 (K), R9.2
unnamed: C17.2, D2.1 (K), L2.1, U8.6 (SW)
unnamed: C31.2, D7.2 (A), Q1.4 (G), R21.2
unnamed: D7.1 (K), Q1.5 (D), Q1.6 (D), Q1.7 (D), Q1.8 (D), SW2.2 (B)
unnamed: D11.2 (A), Q2.4 (G), R31.1, R32.2
unnamed: D12.1 (K), R40.2
unnamed: J1.A5 (CC1), R7.1
unnamed: J1.B5 (CC2), R8.1
unnamed: J1.A6 (D+), J1.B6 (D+), U5.3 (I/O2)
unnamed: J1.A7 (D-), J1.B7 (D-), U5.1 (I/O1)
unnamed: J8.1, Q2.1 (S), Q2.2 (S), Q2.3 (S)
unnamed: J10.A5 (CC1), R35.1
unnamed: J10.B5 (CC2), R36.1
unnamed: J10.A6 (D+), J10.B6 (D+), U13.3 (I/O2)
unnamed: J10.A7 (D-), J10.B7 (D-), U13.1 (I/O1)
unnamed: Q3.3 (C), R32.1
unnamed: J3.1, SW2.1 (A)
unnamed: ESP_BOOT1.2, R3.1, R29.1, U1.10 (IO0)
unnamed: R5.1, U1.9 (IO2)
unnamed: ESP_RST1.2, R28.2, U1.15 (RST)
unnamed: C30.1, U2.8 (5VOUT)
unnamed: R20.1, U2.23 (BRA)
unnamed: R19.1, U2.27 (BRB)
unnamed: C25.1, U2.5 (CPI)
unnamed: C25.2, U2.4 (CPO)
unnamed: R18.1, R39.1, U2.2 (ENN)
unnamed: C28.2, U2.6 (VCP)
unnamed: C39.1, U3.8 (5VOUT)
unnamed: R24.1, U3.23 (BRA)
unnamed: R23.1, U3.27 (BRB)
unnamed: C34.1, U3.5 (CPI)
unnamed: C34.2, U3.4 (CPO)
unnamed: R22.1, R38.1, U3.2 (ENN)
unnamed: C37.2, U3.6 (VCP)
unnamed: J1.A4 (VBUS), J1.A9 (VBUS), J1.B4 (VBUS), J1.B9 (VBUS), U5.5 (VBUS)
unnamed: R12.1, U6.32 (PA11)
unnamed: R13.1, U6.33 (PA12)
unnamed: R33.2, U6.4 (PC15)
unnamed: C6.1, U6.22 (VCAP1)
unnamed: R11.1, U7.3 (EN)
unnamed: C17.1, U8.1 (BS)
unnamed: R10.1, U8.4 (EN)
unnamed: R14.1, R15.2, U8.3 (FB)
unnamed: U12.4 (D+), U13.4 (I/O2)
unnamed: U12.5 (D-), U13.6 (I/O1)
unnamed: C47.1, C48.1, U12.6 (VDD)
unnamed: R34.2, U12.11 (~SUSPEND)

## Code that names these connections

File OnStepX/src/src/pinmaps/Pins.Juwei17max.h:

// -------------------------------------------------------------------------------------------------
// Pin map for FYSETC S6
#pragma once

#if defined(STM32F446xx)

// TX2/RX2 (PA2/PA3) is on the Y+ and Z+ end stops and is reserved for GPS (etc, no command channel is associated with this port)

// Schematic isn't entirely clear, best guess:
// Serial1 RX1 Pin PA10, TX1 Pin PA9
// Serial2 RX2 Pin PA3, TX2 Pin PA2
// Serial3 RX3 Pin PC11, TX3 Pin PC10
// Serial6 RX6 Pin PC7, TX6 Pin PC6

#if SERIAL_A_BAUD_DEFAULT != OFF
 #define SERIAL_A              Serial1
 // #define SERIAL_A              HardSerial
 // #define SERIAL_A_RX           PA10
 // #define SERIAL_A_TX           PA9
#endif

#if SERIAL_B_BAUD_DEFAULT != OFF
  #define SERIAL_B              HardSerial
  #define SERIAL_B_RX           PA3
  #define SERIAL_B_TX           PA2
#endif

#if SERIAL_GPS_BAUD != OFF
  #ifndef SERIAL_GPS
    #define SERIAL_GPS              HardSerial
    #define SERIAL_GPS_RX           PC7
    #define SERIAL_GPS_TX           PC6
  #endif
#endif

#if defined(STEP_DIR_TMC_UART_PRESENT) || defined(SERVO_TMC2209_PRESENT)
  #define SERIAL_TMC_HARDWARE_UART
  #define SERIAL_TMC            Serial3          // Use a single hardware serial port to up to four drivers
  #define SERIAL_TMC_BAUD       115200           // Baud rate
  #define SERIAL_TMC_RX         PC5               // Recieving data
  #define SERIAL_TMC_TX         PB10               // Transmit data
  #define SERIAL_TMC_ADDRESS_MAP(x)   (x) // Axis1(0) is 0, Axis2(1) is 1
  #define SERIAL_TMC_RX_DISABLE false
#endif

#define PIN_INIT() { \
  HAL_WIRE.setSDA(PB7);\
  HAL_WIRE.setSCL(PB6);\
}

  //pinMode(PB0, OUTPUT);\
  //digitalWrite(PB0, HIGH);\

// The multi-purpose pins (Aux3..Aux8 can be analog pwm/dac if supported)
// I defined 7 Aux pins so they match up with the first 7 Auxiliary Feature slots avaliable in OnStep
// Aux1-3 can be used for pretty much anything
// Aux4-7 are more for dew-heaters
//#define AUX1_PIN                FAN0_PIN
//#define AUX2_PIN                FAN1_PIN
//#define AUX3_PIN                FAN2_PIN
//#define AUX4_PIN                HEATER0_PIN
//#define AUX5_PIN                HEATER1_PIN
//#define AUX6_PIN                HEATER2_PIN
//#define AUX7_PIN                HEATER3_PIN

// Misc. pins
//#ifndef DS3234_CS_PIN
//  #define DS3234_CS_PIN         PA4              // Default CS Pin for DS3234 on SPI (on EXP2 shared with the ESP8266 RST pin)
//#endif
//#ifndef BMx280_CS_PIN
//  #define BMx280_CS_PIN         PC7              // Default CS Pin for BME280/BMP280 on SPI (on EXP2 shared with LED2/Reticle)
//#endif
#ifndef ONE_WIRE_PIN
  #define ONE_WIRE_PIN          PC10              // Default Pin for OneWire bus (on E2-MOT PD-EN, right hand pin)
#endif
#define ADDON_GPIO0_PIN         PA1              // ESP8266 GPIO0 (on EXP1)
#define ADDON_RESET_PIN         PA4              // ESP8266 RST (on EXP2 shared with the DS3234 CS pin)

// The PEC index sense is a logic level input, resets the PEC index on rising edge then waits for 60 seconds before allowing another reset
#ifndef PEC_SENSE_PIN
#define PEC_SENSE_PIN           PB9              // PEC Sense, analog or digital (on X+ so it can have 3v3 or 5v on adjacent pin)
#endif

// The status LED is a two wire jumper with a 10k resistor in series to limit the current to the LED
#define STATUS_LED_PIN        PC13              // Drain (on EXP2) One could perhaps move these to the RGB leds, there's a header but no +5V present on it.
#define MOUNT_LED_PIN         PC12              // Drain (on EXP2 shared with Reticle/BME280_CS)

// The PPS pin is a 3.3V logic input, OnStep measures time between rising edges and adjusts the internal sidereal clock frequency
#ifndef PPS_SENSE_PIN
  #define PPS_SENSE_PIN         PB8          // PPS time source, GPS for example (on EXP2)
#endif

#ifndef LIMIT_SENSE_PIN
  #define LIMIT_SENSE_PIN       PA0              // Limit switch sense (on Z-)
#endif

//#define SHARED_ENABLE_PIN       PB0  
#define DEDICATED_MODE_PINS

// Axis1 RA/Azm step/dir driver
#define AXIS1_ENABLE_PIN        PB0
#define AXIS1_M0_PIN            PB3          // SPI MOSI
#define AXIS1_M1_PIN            PB4           // SPI SCK
#define AXIS1_M2_PIN            PA5              // SPI CS (UART TX)
#define AXIS1_M3_PIN            PA7          // SPI MISO (UART RX)
#define AXIS1_STEP_PIN          PB1
#define AXIS1_DIR_PIN           PC8
#define AXIS1_SENSE_HOME_PIN    PB14             // (on X-)


// Axis2 Dec/Alt step/dir driver
#define AXIS2_ENABLE_PIN        PB0
#define AXIS2_M0_PIN            PB5          // SPI MOSI
#define AXIS2_M1_PIN            PB12           // SPI SCK
#define AXIS2_M2_PIN            PA6             // SPI CS (UART TX)
#define AXIS2_M3_PIN            PA8        // SPI MISO (UART RX)
#define AXIS2_STEP_PIN          PC9
#define AXIS2_DIR_PIN           PA15
#define AXIS2_SENSE_HOME_PIN    PB13             // (on Y-)


// For rotator stepper driver
//#define AXIS3_ENABLE_PIN        PD15
//#define AXIS3_M0_PIN            SS_MOSI          // SPI MOSI
//#define AXIS3_M1_PIN            SS_SCK           // SPI SCK
//#define AXIS3_M2_PIN            PD10             // SPI CS (UART TX)
//#define AXIS3_M3_PIN            SS_MISO          // SPI MISO (UART RX)
//#define AXIS3_STEP_PIN          PD14
//#define AXIS3_DIR_PIN           PD13

// For focuser1 stepper driver
//#define AXIS4_ENABLE_PIN        PD4
//#define AXIS4_M0_PIN            SS_MOSI          // SPI MOSI
//#define AXIS4_M1_PIN            SS_SCK           // SPI SCK
//#define AXIS4_M2_PIN            PD7              // SPI CS (UART TX)
//#define AXIS4_M3_PIN            SS_MISO          // SPI MISO (UART RX)
//#define AXIS4_STEP_PIN          PD5
//#define AXIS4_DIR_PIN           PD6

// For focuser2 stepper driver
//#define AXIS5_ENABLE_PIN        PE5
//#define AXIS5_M0_PIN            SS_MOSI          // SPI MOSI
//#define AXIS5_M1_PIN            SS_SCK           // SPI SCK
//#define AXIS5_M2_PIN            PC14             // SPI CS (UART TX)
//#define AXIS5_M3_PIN            SS_MISO          // SPI MISO (UART RX)
//#define AXIS5_STEP_PIN          PE6
//#define AXIS5_DIR_PIN           PC13

// For focuser3 stepper driver
//#define AXIS6_ENABLE_PIN        PE3
//#define AXIS6_M0_PIN            SS_MOSI          // SPI MOSI
//#define AXIS6_M1_PIN            SS_SCK           // SPI SCK
//#define AXIS6_M2_PIN            PC15             // SPI CS (UART TX)
//#define AXIS6_M3_PIN            SS_MISO          // SPI MISO (UART RX)
//#define AXIS6_STEP_PIN          PE2
//#define AXIS6_DIR_PIN           PE4

// ST4 interface
#define ST4_RA_W_PIN            PC0              // ST4 RA- West  (on EXP1)
#define ST4_DEC_S_PIN           PC2              // ST4 DE- South (on EXP1)
#define ST4_DEC_N_PIN           PC1             // ST4 DE+ North (on EXP1)
#define ST4_RA_E_PIN            PC3              // ST4 RA+ East  (on EXP1)

#else
#error "Wrong processor for this configuration!"

#endif

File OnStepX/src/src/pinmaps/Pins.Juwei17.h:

// -------------------------------------------------------------------------------------------------
// Pin map for OnStep MaxSTM STM32F411CE/STM32F401CE PCB (or the Blackpill https://github.com/WeActTC/MiniF4-STM32F4x1)
#pragma once

#if defined(STM32F411xE) || defined(STM32F401xC)

// For an 8KB EEPROM on the MaxSTM3.6I
//#define NV_M24C64


// Serial ports (see Pins.defaults.h for SERIAL_A)
// Serial1 RX1 Pin PA10, TX1 Pin PA9
// Serial2 RX2 Pin PA3 , TX2 Pin PA2
// Serial6 RX6 Pin PA12, TX6 Pin PA11 (used for USB virtual serial)

#define DEDICATED_MODE_PINS

#if defined(STEP_DIR_TMC_UART_PRESENT) || defined(SERVO_TMC2209_PRESENT)
//  #define DRIVER_TMC_STEPPER
  #define SERIAL_TMC_RX               PA6
  #define SERIAL_TMC_TX               PB9
  #define SERIAL_TMC_BAUD             9600 
  #define SERIAL_TMC_ADDRESS_MAP(x)   ((x==4)?2 : x) // Axis1(0) is 0, Axis2(1) is 1, Axis3(2) is 2, Axis4(3) is 3, Axis5(4) is 2
  #define SERIAL_TMC_RX_DISABLE false
#endif

#define PIN_INIT() { \
  pinMode(PB9, OUTPUT);\
  digitalWrite(PB9, HIGH);\
}


#if SERIAL_A_BAUD_DEFAULT != OFF
  #define SERIAL_A              Serial
#endif
#if SERIAL_B_BAUD_DEFAULT != OFF
  #define SERIAL_B              HardSerial
  #define SERIAL_B_RX           PA3
  #define SERIAL_B_TX           PA2
#endif
#if SERIAL_C_BAUD_DEFAULT != OFF
  #define SERIAL_C              HardSerial
  #define SERIAL_C_RX           PA10
  #define SERIAL_C_TX           PA9
#endif

// Auto assign the Serial1 port pins for GPS
#if SERIAL_GPS_BAUD != OFF
  #ifndef SERIAL_GPS
    #define SERIAL_GPS          HardSerial
    #define SERIAL_GPS_RX       PA10
    #define SERIAL_GPS_TX       PA9
  #endif
#endif

// Misc. pins
#ifndef ONE_WIRE_PIN
  #define ONE_WIRE_PIN          OFF         // Default Pin for OneWire bus (note: this pin has a 0.1uF capacitor that must be removed for OneWire to function)
#endif
#define ADDON_GPIO0_PIN         PA14              // ESP8266 GPIO0 (shared with AXIS2_DIR_PIN)
#define ADDON_RESET_PIN         PA8              // ESP8266 RST

// The PEC index sense is a logic level input, resets the PEC index on rising edge then waits for 60 seconds before allowing another reset
#ifndef PEC_SENSE_PIN
  #define PEC_SENSE_PIN         OFF              // PEC Sense, analog or digital
#endif

// The status LED is a two wire jumper with a 10k resistor in series to limit the current to the LED
#define STATUS_LED_PIN          PB12         // Default LED Cathode (-)
#define MOUNT_LED_PIN           OFF         // Default LED Cathode (-)
#ifndef RETICLE_LED_PIN
  #define RETICLE_LED_PIN       OFF         // Default LED Cathode (-)
#endif

// For a piezo buzzer
#define STATUS_BUZZER_PIN       OFF             // Tone

// The PPS pin is a 3.3V logic input, OnStep measures time between rising edges and adjusts the internal sidereal clock frequency
#ifndef PPS_SENSE_PIN
    #define PPS_SENSE_PIN       PA13         // PPS time source, GPS for example (MaxSTM version 3.61 and later)
#endif

// The limit switch sense is a logic level input normally pull high (2k resistor,) shorted to ground it stops gotos/tracking
#ifndef LIMIT_SENSE_PIN
  #define LIMIT_SENSE_PIN       PB15
#endif

#define SHARED_ENABLE_PIN       PB8    
// Axis1 RA/Azm step/dir driver
#define AXIS1_ENABLE_PIN        SHARED
#define AXIS1_M0_PIN            OFF
#define AXIS1_M1_PIN            OFF
#define AXIS1_M2_PIN            PB9        // UART TX
#define AXIS1_M3_PIN            PA6         // UART RX
#define AXIS1_STEP_PIN          PB10
#define AXIS1_DIR_PIN           PB2
#define AXIS1_SENSE_HOME_PIN    PB13

// Axis2 Dec/Alt step/dir driver
#define AXIS2_ENABLE_PIN        SHARED
#define AXIS2_M0_PIN            OFF
#define AXIS2_M1_PIN            OFF
#define AXIS2_M2_PIN            PB9        // UART TX
#define AXIS2_M3_PIN            PA6         // UART RX
#define AXIS2_STEP_PIN          PA4
#define AXIS2_DIR_PIN           PB0
#define AXIS2_SENSE_HOME_PIN    PB14


// For rotator stepper driver
#define SHARED_DIRECTION_PINS                    // Hint that the direction pins are shared
#define AXIS3_ENABLE_PIN        OFF
#define AXIS3_M0_PIN            OFF              // SPI MOSI
#define AXIS3_M1_PIN            OFF              // SPI SCK
#define AXIS3_M2_PIN            OFF             // SPI CS (UART TX)
#define AXIS3_M3_PIN            OFF         // SPI MISO (UART RX)
#define AXIS3_STEP_PIN          OFF
#define AXIS3_DIR_PIN           OFF

// For focuser1 stepper driver
#define AXIS4_ENABLE_PIN        OFF
#define AXIS4_M0_PIN            OFF              // SPI MOSI
#define AXIS4_M1_PIN            OFF              // SPI SCK
#define AXIS4_M2_PIN            OFF             // SPI CS (UART TX)
#define AXIS4_M3_PIN            OFF         // SPI MISO (UART RX)
#define AXIS4_STEP_PIN          OFF
#define AXIS4_DIR_PIN           OFF

// For focuser2 stepper driver
#define AXIS5_ENABLE_PIN        OFF
#define AXIS5_M0_PIN            OFF              // SPI MOSI
#define AXIS5_M1_PIN            OFF              // SPI SCK
#define AXIS5_M2_PIN            OFF             // SPI CS (UART TX)
#define AXIS5_M3_PIN            OFF         // SPI MISO (UART RX)
#define AXIS5_STEP_PIN          OFF
#define AXIS5_DIR_PIN           OFF

// ST4 interface
#define ST4_RA_W_PIN            PA15             // ST4 RA- West
#define ST4_DEC_S_PIN           PB3              // ST4 DE- South
#define ST4_DEC_N_PIN           PB4              // ST4 DE+ North
#define ST4_RA_E_PIN            PB5              // ST4 RA+ East

#else
#error "Wrong processor for this configuration!"

#endif

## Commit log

2025-08-10 readme update
2025-08-10 HW, onstepx
2025-08-10 refomrated readme
2025-08-10 onstepx src
2025-08-14 pictures, stls
2025-08-17 update firmware selection
2025-08-17 cleanup
2025-08-17 added homing ring stl
2025-08-17 formatting, typos
2025-08-17 typos
